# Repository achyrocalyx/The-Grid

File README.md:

# The-Grid
EC REX Small Build Project (Interactive LED Floor)

Funded in part by the Council for the Arts at MIT. [@artsatMIT](https://www.instagram.com/artsatmit/)

With generous support from [EasyEDA](https://easyeda.com/) and [JLCPCB](https://jlcpcb.com/) for PCB manufacturing.

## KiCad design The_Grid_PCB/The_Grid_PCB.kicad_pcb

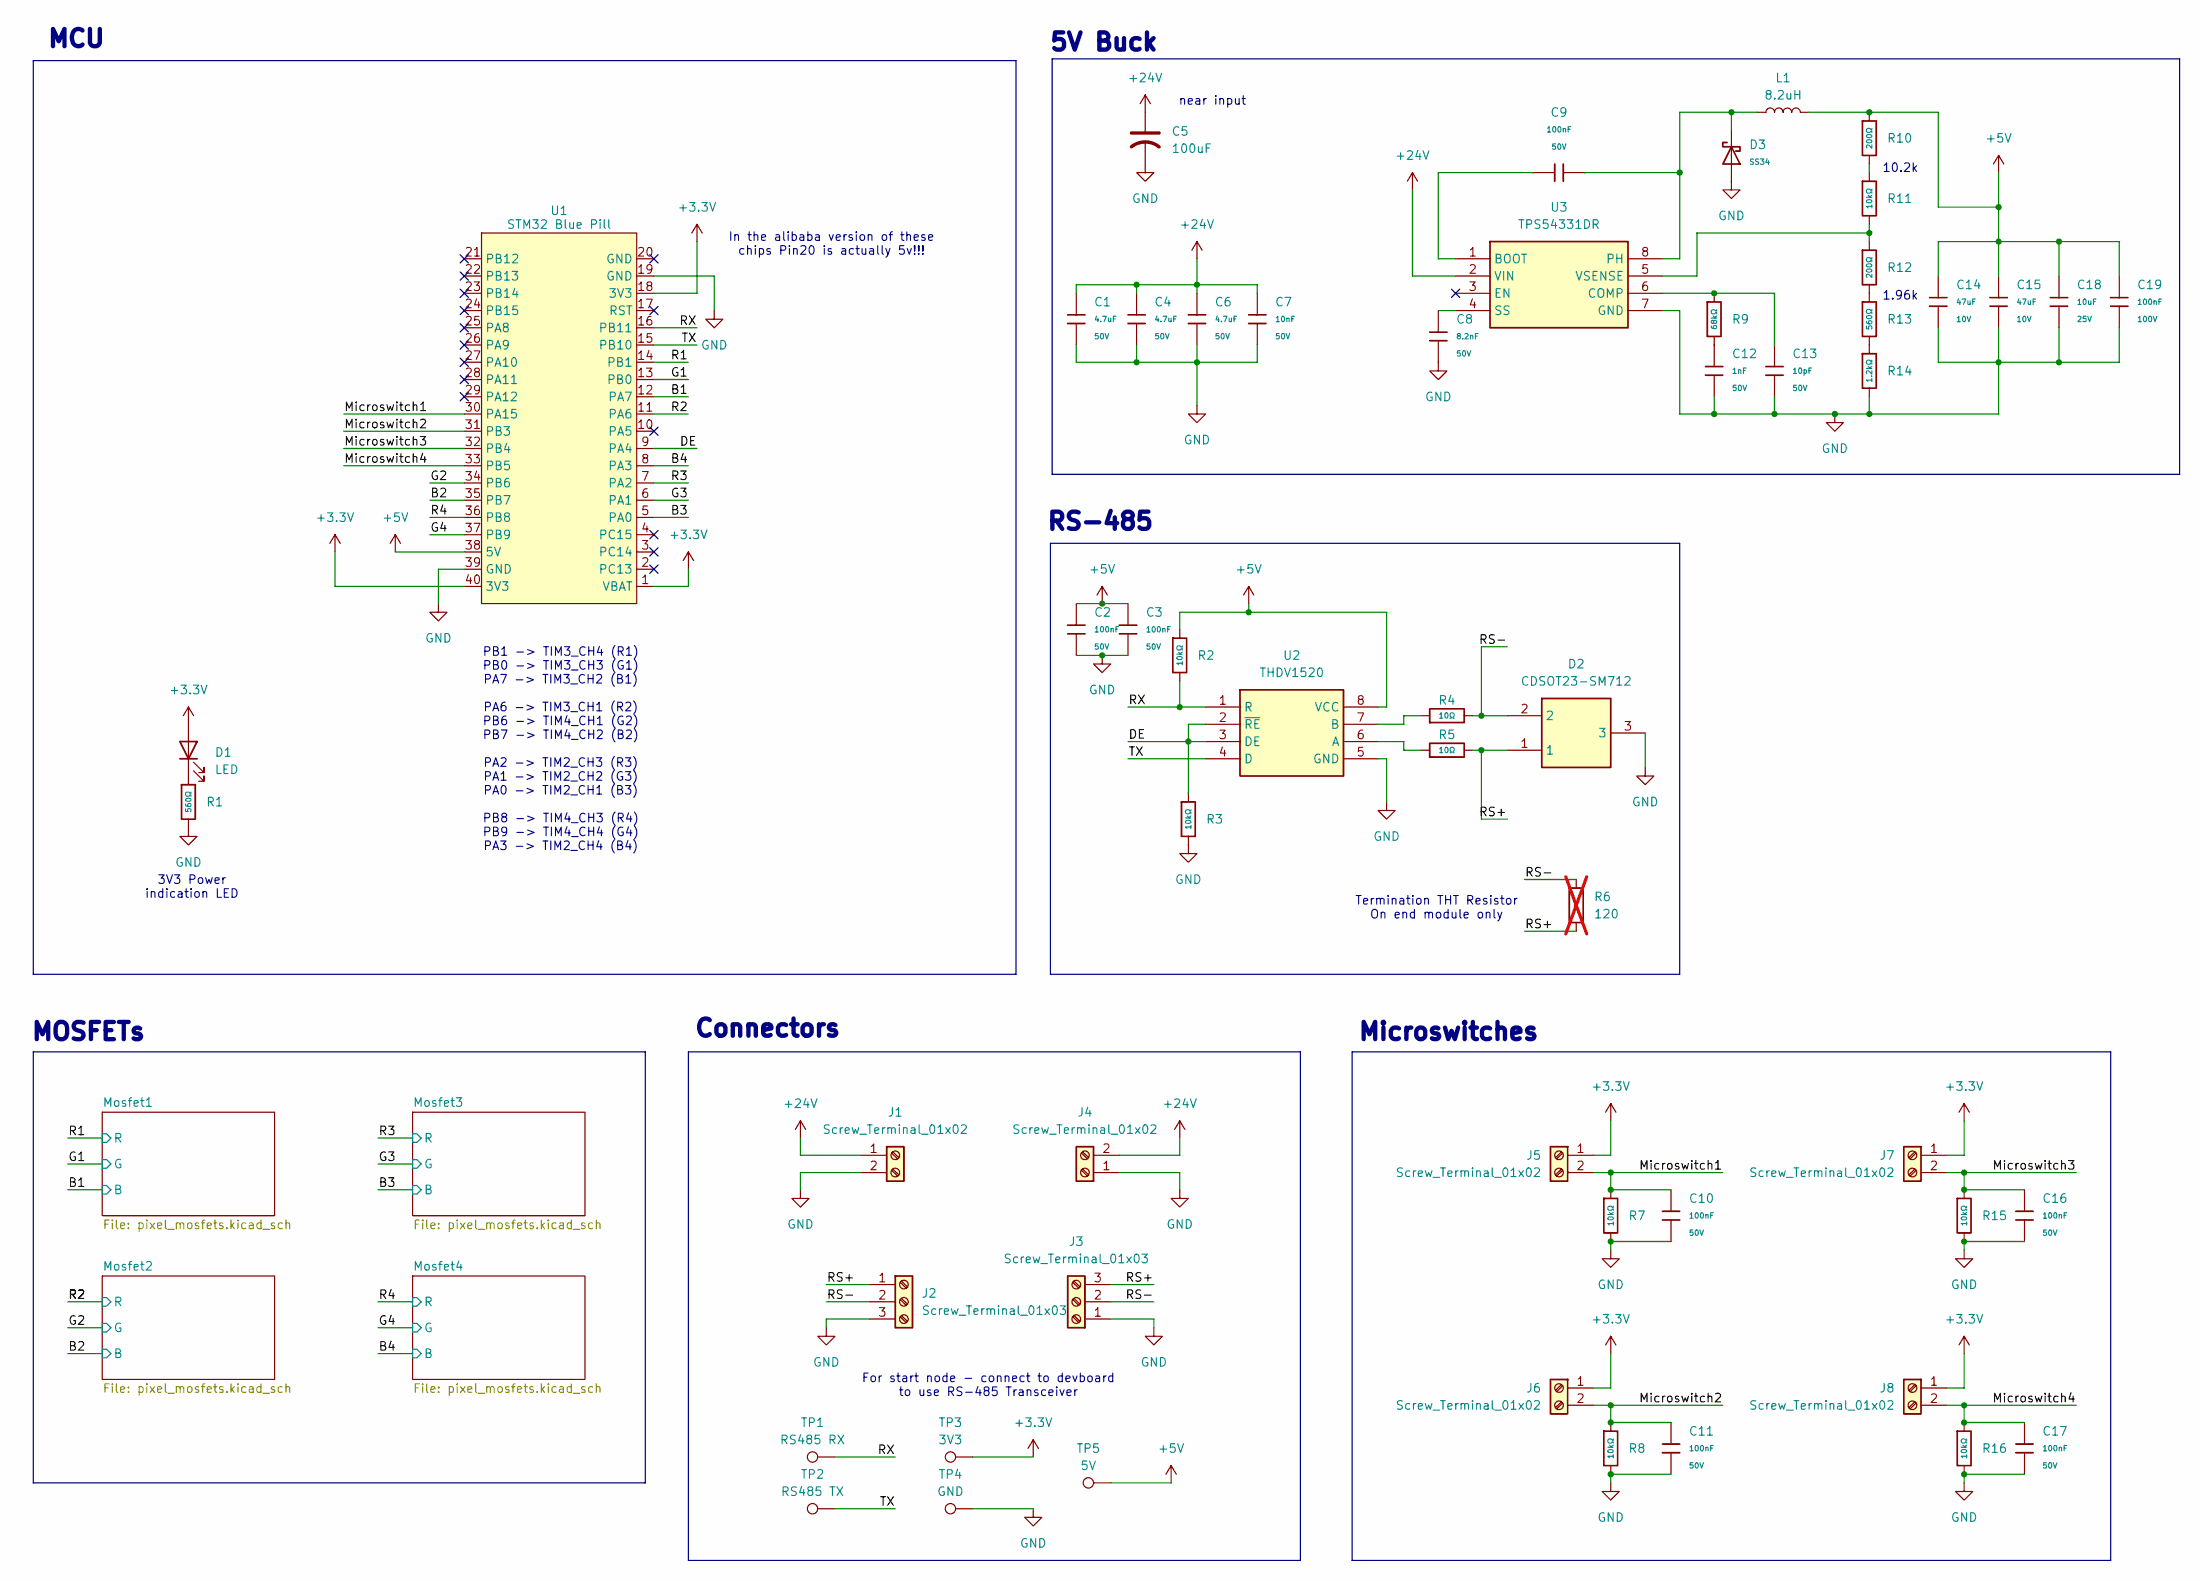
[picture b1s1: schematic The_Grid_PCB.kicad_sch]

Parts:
C1, C4, C6: 4.7uF; C_1206; Voltage Rated 50V; Tolerance ±10%; Part 1206B475K500NT; LCSC C29823
C2, C3, C9, C10, C11, C16, C17: 100nF; C_0603; Voltage Rated 50V; Tolerance ±10%; Part CC0603KRX7R9BB104; LCSC C14663
C5: 100uF; CP_Radial_D8.0mm_P3.50mm; LCSC C112510
C7: 10nF; C_0805; Voltage Rated 50V; Tolerance ±10%; Part CL21B103KBANNNC; LCSC C1710
C8: 8.2nF; C_0603; Voltage Rated 50V; Tolerance ±10%; Part 0603B822K500NT; LCSC C1322360
C12: 1nF; C_0805; Voltage Rated 50V; Tolerance ±10%; Part CL21B102KBCNNNC; LCSC C46653
C13: 10pF; C_0603; Voltage Rated 50V; Tolerance ±5%; Part CL10C100JB8NNNC; LCSC C1634
C14, C15: 47uF; C_1206; Voltage Rated 10V; Tolerance ±20%; Part CL31A476MPHNNNE; LCSC C96123
C18: 10uF; C_0805; Voltage Rated 25V; Tolerance ±10%; Part CL21A106KAYNNNE; LCSC C15850
C19: 100nF; C_0805; Voltage Rated 100V; Tolerance ±10%; Part CL21B104KCFNNNE; LCSC C28233
D1: LED; D_0603; LCSC C2286
D2: CDSOT23-SM712; SOT-23; Manufacturer_Part_Number CDSOT23-SM712; Mouser Part Number 652-CDSOT23-SM712
D3: SS34; D_SMA; Forward Voltage (Vf@If) 550mV@3A; Reverse Voltage (Vr) 40V; Part SS34; LCSC C8678
J1, J4: Screw_Terminal_01x02; TerminalBlock_MaiXu_MX126-5.0-02P_1x02_P5.00mm; LCSC C8404
J2, J3: Screw_Terminal_01x03; TerminalBlock_Xinya_XY308-2.54-3P_1x03_P2.54mm_Horizontal; LCSC C5188443
J5, J6, J7, J8: Screw_Terminal_01x02; TerminalBlock_4Ucon_1x02_P3.50mm_Horizontal; LCSC C695629
L1: 8.2uH; L_Bourns_SRP7028A_7.3x6.6mm; LCSC C167222
R1, R13: 560Ω; R_0603; Overload Voltage (Max) 75V; Tolerance ±1%; Part 0603WAF5600T5E; LCSC C23204
R2, R3, R7, R8, R11, R15, R16: 10kΩ; R_0603; Overload Voltage (Max) 75V; Tolerance ±1%; Part 0603WAF1002T5E; LCSC C25804
R4, R5: 10Ω; R_0603; Overload Voltage (Max) 75V; Tolerance ±1%; Part 0603WAF100JT5E; LCSC C22859
R6: 120; R_Axial_DIN0207_L6.3mm_D2.5mm_P10.16mm_Horizontal; not fitted
R9: 68kΩ; R_0603; Overload Voltage (Max) 75V; Tolerance ±1%; Part 0603WAF6802T5E; LCSC C23231
R10, R12: 200Ω; R_0603; Overload Voltage (Max) 75V; Tolerance ±1%; Part 0603WAF2000T5E; LCSC C8218
R14: 1.2kΩ; R_0603; Overload Voltage (Max) 75V; Tolerance ±1%; Part 0603WAF1201T5E; LCSC C22765
TP1: RS485 RX; TestPoint_THTPad_D2.0mm_Drill1.0mm
TP2: RS485 TX; TestPoint_THTPad_D2.0mm_Drill1.0mm
TP3: 3V3; TestPoint_THTPad_D2.0mm_Drill1.0mm
TP4: GND; TestPoint_THTPad_D2.0mm_Drill1.0mm
TP5: 5V; TestPoint_THTPad_D2.0mm_Drill1.0mm
U1: STM32 Blue Pill; STM32BluePill
U2: THDV1520; SOIC-8_3.9x4.9mm_P1.27mm; Manufacturer_Part_Number THDV1520; LCSC C882408
U3: TPS54331DR; SOIC127P600X175-8N; Manufacturer_Part_Number TPS54331DR; Mouser Part Number 595-TPS54331DR

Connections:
+3.3V: D1.2 (A), J5.1, J6.1, J7.1, J8.1, TP3.1 (1_1), U1.1 (VBAT), U1.18 (3V3), U1.40 (3V3)
+5V: C2.1, C3.1, C14.2, C15.2, C18.1, C19.1, L1.2, R2.1, R10.1, TP5.1 (1_1), U1.38 (5V), U2.8 (VCC)
+24V: C1.1, C4.1, C5.1, C6.1, C7.1, J1.1, J4.2, U3.2 (VIN); also elsewhere on the board
/B1: U1.12 (PA7); also elsewhere on the board
/B2: U1.35 (PB7); also elsewhere on the board
/B3: U1.5 (PA0); also elsewhere on the board
/B4: U1.8 (PA3); also elsewhere on the board
/DE: R3.1, U1.9 (PA4), U2.2 (~RE), U2.3 (DE)
/G1: U1.13 (PB0); also elsewhere on the board
/G2: U1.34 (PB6); also elsewhere on the board
/G3: U1.6 (PA1); also elsewhere on the board
/G4: U1.37 (PB9); also elsewhere on the board
/Microswitch1: C10.1, J5.2, R7.1, U1.30 (PA15)
/Microswitch2: C11.1, J6.2, R8.1, U1.31 (PB3)
/Microswitch3: C16.1, J7.2, R15.1, U1.32 (PB4)
/Microswitch4: C17.1, J8.2, R16.1, U1.33 (PB5)
/R1: U1.14 (PB1); also elsewhere on the board
/R2: U1.11 (PA6); also elsewhere on the board
/R3: U1.7 (PA2); also elsewhere on the board
/R4: U1.36 (PB8); also elsewhere on the board
/RS+: D2.1, J2.1, J3.3, R5.2, R6.2
/RS-: D2.2, J2.2, J3.2, R4.2, R6.1
/RX: R2.2, TP1.1 (1_1), U1.16 (PB11), U2.1 (R)
/TX: TP2.1 (1_1), U1.15 (PB10), U2.4 (D)
GND: C1.2, C2.2, C3.2, C4.2, C5.2, C6.2, C7.2, C8.2, C10.2, C11.2, C12.2, C13.2, C14.1, C15.1, C16.2, C17.2, C18.2, C19.2, D2.3, D3.2, J1.2, J2.3, J3.1, J4.1, R1.2, R3.2, R7.2, R8.2, R14.2, R15.2, R16.2, TP4.1 (1_1), U1.19 (GND), U1.39 (GND), U2.5 (GND), U3.7 (GND); also elsewhere on the board
unnamed: C12.1, R9.2
unnamed: D1.1 (K), R1.1
unnamed: R10.2, R11.1
unnamed: R12.2, R13.1
unnamed: R13.2, R14.1
unnamed: R5.1, U2.6 (A)
unnamed: R4.1, U2.7 (B)
unnamed: C9.1, U3.1 (BOOT)
unnamed: C13.1, R9.1, U3.6 (COMP)
unnamed: C9.2, D3.1, L1.1, U3.8 (PH)
unnamed: C8.1, U3.4 (SS)
unnamed: R11.2, R12.1, U3.5 (VSENSE)

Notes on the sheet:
RS-485
Connectors
1.96k
In the alibaba version of these chips Pin20 is actually 5v!!!
For start node - connect to devboard to use RS-485 Transceiver
3V3 Power indication LED
10.2k
5V Buck
near input
PB1 -> TIM3_CH4 (R1) PB0 -> TIM3_CH3 (G1) PA7 -> TIM3_CH2 (B1) PA6 -> TIM3_CH1 (R2) PB6 -> TIM4_CH1 (G2) PB7 -> TIM4_CH2 (B2) PA2 -> TIM2_CH3 (R3) PA1 -> TIM2_CH2 (G3) PA0 -> TIM2_CH1 (B3) PB8 -> TIM4_CH3 (R4) PB9 -> TIM4_CH4 (G4) PA3 -> TIM2_CH4 (B4)
MOSFETs
MCU
Termination THT Resistor On end module only
Microswitches

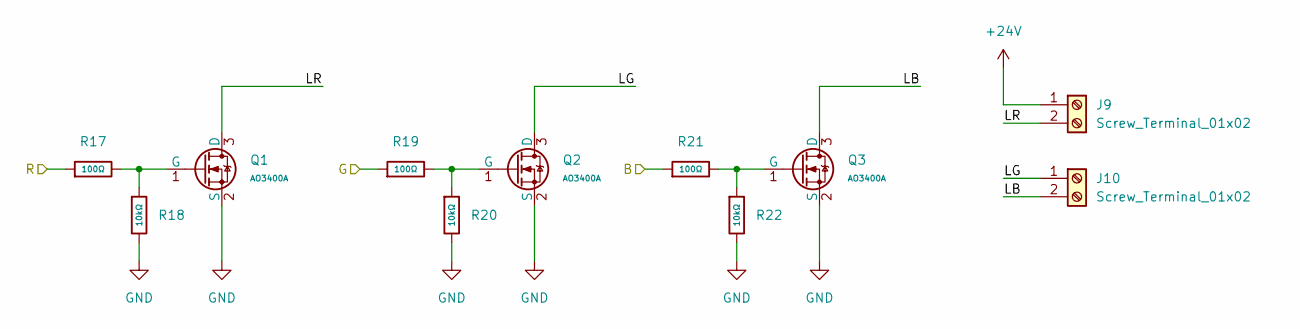
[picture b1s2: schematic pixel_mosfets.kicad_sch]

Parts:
J9, J10: Screw_Terminal_01x02; TerminalBlock_4Ucon_1x02_P3.50mm_Horizontal; LCSC C695629
Q1, Q2, Q3: AO3400A; Q_SOT-23; Part AO3400A; LCSC C20917
R17, R19, R21: 100Ω; R_0603; Overload Voltage (Max) 75V; Tolerance ±1%; Part 0603WAF1000T5E; LCSC C22775
R18, R20, R22: 10kΩ; R_0603; Overload Voltage (Max) 75V; Tolerance ±1%; Part 0603WAF1002T5E; LCSC C25804

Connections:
+24V: J9.1; also elsewhere on the board
/B1: R21.1; also elsewhere on the board
/G1: R19.1; also elsewhere on the board
/Mosfet1/LB: J10.2, Q3.3 (D)
/Mosfet1/LG: J10.1, Q2.3 (D)
/Mosfet1/LR: J9.2, Q1.3 (D)
/R1: R17.1; also elsewhere on the board
GND: Q1.2 (S), Q2.2 (S), Q3.2 (S), R18.2, R20.2, R22.2; also elsewhere on the board
unnamed: Q1.1 (G), R17.2, R18.1
unnamed: Q2.1 (G), R19.2, R20.1
unnamed: Q3.1 (G), R21.2, R22.1

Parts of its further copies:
J11, J12, J13, J14, J15, J16: Screw_Terminal_01x02; TerminalBlock_4Ucon_1x02_P3.50mm_Horizontal; LCSC C695629
Q4, Q5, Q6, Q7, Q8, Q9, Q10, Q11, Q12: AO3400A; Q_SOT-23; Part AO3400A; LCSC C20917
R23, R25, R27, R29, R31, R33, R35, R37, R39: 100Ω; R_0603; Overload Voltage (Max) 75V; Tolerance ±1%; Part 0603WAF1000T5E; LCSC C22775
R24, R26, R28, R30, R32, R34, R36, R38, R40: 10kΩ; R_0603; Overload Voltage (Max) 75V; Tolerance ±1%; Part 0603WAF1002T5E; LCSC C25804

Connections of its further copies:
+24V: J11.1, J13.1, J15.1; also elsewhere on the board
/B2: R27.1; also elsewhere on the board
/B3: R33.1; also elsewhere on the board
/B4: R39.1; also elsewhere on the board
/G2: R25.1; also elsewhere on the board
/G3: R31.1; also elsewhere on the board
/G4: R37.1; also elsewhere on the board
/Mosfet2/LB: J12.2, Q6.3 (D)
/Mosfet2/LG: J12.1, Q5.3 (D)
/Mosfet2/LR: J11.2, Q4.3 (D)
/Mosfet3/LB: J14.2, Q9.3 (D)
/Mosfet3/LG: J14.1, Q8.3 (D)
/Mosfet3/LR: J13.2, Q7.3 (D)
/Mosfet4/LB: J16.2, Q12.3 (D)
/Mosfet4/LG: J16.1, Q11.3 (D)
/Mosfet4/LR: J15.2, Q10.3 (D)
/R2: R23.1; also elsewhere on the board
/R3: R29.1; also elsewhere on the board
/R4: R35.1; also elsewhere on the board
GND: Q4.2 (S), Q5.2 (S), Q6.2 (S), Q7.2 (S), Q8.2 (S), Q9.2 (S), Q10.2 (S), Q11.2 (S), Q12.2 (S), R24.2, R26.2, R28.2, R30.2, R32.2, R34.2, R36.2, R38.2, R40.2; also elsewhere on the board
unnamed: Q4.1 (G), R23.2, R24.1
unnamed: Q5.1 (G), R25.2, R26.1
unnamed: Q6.1 (G), R27.2, R28.1
unnamed: Q7.1 (G), R29.2, R30.1
unnamed: Q8.1 (G), R31.2, R32.1
unnamed: Q9.1 (G), R33.2, R34.1
unnamed: Q10.1 (G), R35.2, R36.1
unnamed: Q11.1 (G), R37.2, R38.1
unnamed: Q12.1 (G), R39.2, R40.1

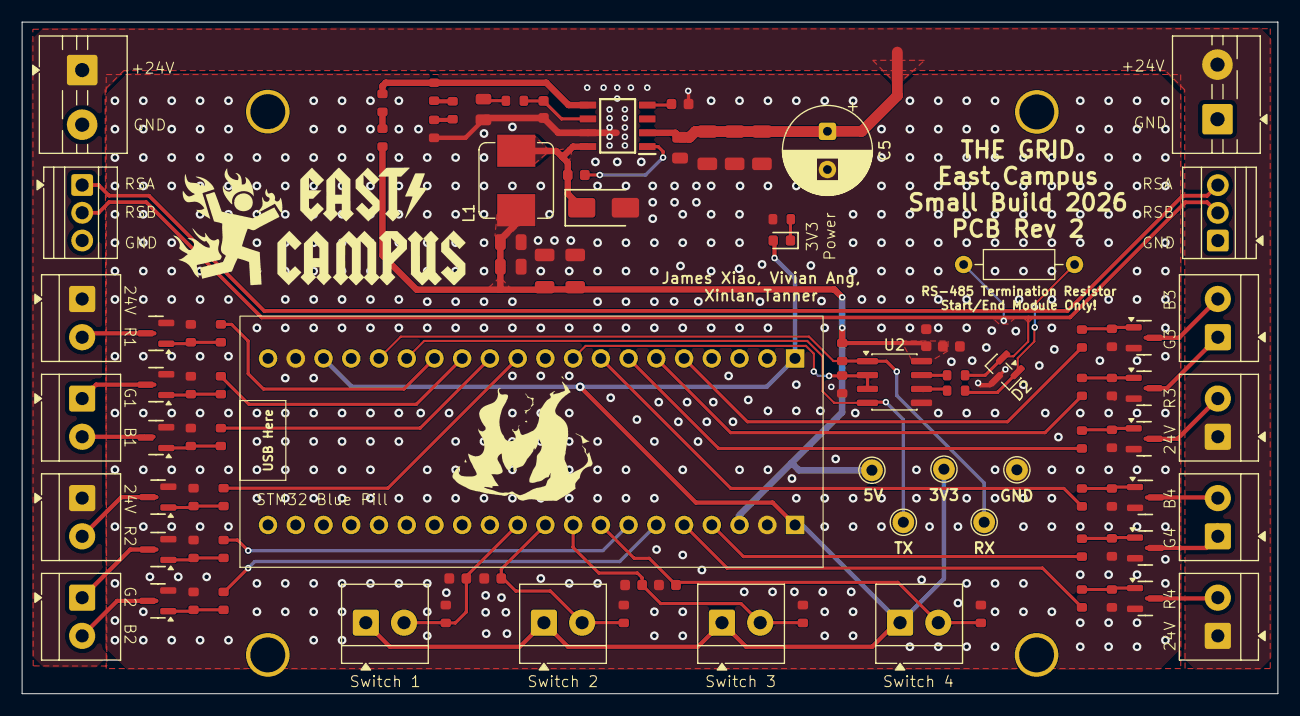
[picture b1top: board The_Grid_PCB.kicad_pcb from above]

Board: 2 copper layers, 115.0 x 61.5 mm, 99 parts (0 on the bottom side), 61 nets.

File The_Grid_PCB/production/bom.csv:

Designator,Footprint,Quantity,Value,LCSC Part #
"C1, C4, C6",C_1206,3,4.7uF,C29823
"C10, C11, C16, C17, C2, C3, C9",C_0603,7,100nF,C14663
C12,C_0805,1,1nF,C46653
C13,C_0603,1,10pF,C1634
"C14, C15",C_1206,2,47uF,C96123
C18,C_0805,1,10uF,C15850
C19,C_0805,1,100nF,C28233
C5,CP_Radial_D8.0mm_P3.50mm,1,100uF,C112510
C7,C_0805,1,10nF,C1710
C8,C_0603,1,8.2nF,C1322360
D1,D_0603,1,LED,C2286
D2,SOT-23,1,CDSOT23-SM712,C404012
D3,D_SMA,1,SS34,C8678
"J1, J4",TerminalBlock_MaiXu_MX126-5.0-02P_1x02_P5.00mm,2,Screw_Terminal_01x02,C8404
"J10, J11, J12, J13, J14, J15, J16, J5, J6, J7, J8, J9",TerminalBlock_4Ucon_1x02_P3.50mm_Horizontal,12,Screw_Terminal_01x02,C695629
"J2, J3",TerminalBlock_Xinya_XY308-2.54-3P_1x03_P2.54mm_Horizontal,2,Screw_Terminal_01x03,C5188443
L1,L_Bourns_SRP7028A_7.3x6.6mm,1,8.2uH,C167222
"Q1, Q10, Q11, Q12, Q2, Q3, Q4, Q5, Q6, Q7, Q8, Q9",Q_SOT-23,12,AO3400A,C20917
"R1, R13",R_0603,2,560Ω,C23204
"R10, R12",R_0603,2,200Ω,C8218
"R11, R15, R16, R18, R2, R20, R22, R24, R26, R28, R3, R30, R32, R34, R36, R38, R40, R7, R8",R_0603,19,10kΩ,C25804
R14,R_0603,1,1.2kΩ,C22765
"R17, R19, R21, R23, R25, R27, R29, R31, R33, R35, R37, R39",R_0603,12,100Ω,C22775
"R4, R5",R_0603,2,10Ω,C22859
R9,R_0603,1,68kΩ,C23231
TP1,TestPoint_THTPad_D2.0mm_Drill1.0mm,1,RS485 RX,
TP2,TestPoint_THTPad_D2.0mm_Drill1.0mm,1,RS485 TX,
TP3,TestPoint_THTPad_D2.0mm_Drill1.0mm,1,3V3,
TP4,TestPoint_THTPad_D2.0mm_Drill1.0mm,1,GND,
TP5,TestPoint_THTPad_D2.0mm_Drill1.0mm,1,5V,
U1,STM32BluePill,1,STM32 Blue Pill,
U2,SOIC-8_3.9x4.9mm_P1.27mm,1,THDV1520,C882408
U3,SOIC127P600X175-8N,1,TPS54331DR,C9865

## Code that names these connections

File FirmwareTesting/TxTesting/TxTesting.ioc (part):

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Mcu.Name=STM32F103C(8-B)Tx
Mcu.Package=LQFP48
Mcu.UserName=STM32F103C8Tx
PA0-WKUP.Signal=S_TIM2_CH1_ETR
PA1.Signal=S_TIM2_CH2
PA15.GPIOParameters=GPIO_ModeDefaultEXTI
PA15.GPIO_ModeDefaultEXTI=GPIO_MODE_IT_RISING
PA15.Signal=GPXTI15
PA2.Signal=S_TIM2_CH3
PA3.Signal=S_TIM2_CH4
PA4.Signal=GPIO_Output
PA6.Signal=S_TIM3_CH1
PA7.Signal=S_TIM3_CH2
PB0.Signal=S_TIM3_CH3
PB1.Signal=S_TIM3_CH4
PB10.Mode=Asynchronous
PB10.Signal=USART3_TX
PB11.Mode=Asynchronous
PB11.Signal=USART3_RX
PB3.Signal=GPXTI3
PB4.Signal=GPXTI4
PB5.Signal=GPXTI5
PB6.Signal=S_TIM4_CH1
PB7.Signal=S_TIM4_CH2
PB8.Signal=S_TIM4_CH3
PB9.Signal=S_TIM4_CH4
PC13-TAMPER-RTC.Signal=GPIO_Output
board=custom

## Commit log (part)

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2026-05-02 iter 1 minus capacitor stuff
2026-05-02 update custom symbols
2026-05-03 module CAD
2026-05-04 draft 1 schematic
2026-05-10 pcb iter 1 done
2026-05-10 upload wiring diagram
2026-05-13 updated CAD
2026-05-13 better organization (aka one folder)
2026-05-14 update wiring diagram again sob
2026-05-31 revised pcb nevin/miguel feedback
2026-05-31 add silkscreen, move termination res
2026-05-31 edit silkscreen
2026-06-03 rev1 pcb sent to prod
2026-06-13 project setup, blink sketch
2026-06-14 microswitch 1 controls led rainbow 1
2026-06-14 standoff cad
2026-06-14 standoff cad but 3mf file this time :(
2026-06-14 mount
2026-06-14 standoff hole too small :()
2026-06-14 mount 2.0
2026-06-14 rs485 testing scripts
2026-06-14 2 pixel test script
2026-06-15 bleh
2026-06-17 2pixel with 100ms req time, still does not fix aoe bug
2026-06-19 ITS SO OVER
2026-06-20 WERE SO BACK
2026-06-26 frame protocol diagram
